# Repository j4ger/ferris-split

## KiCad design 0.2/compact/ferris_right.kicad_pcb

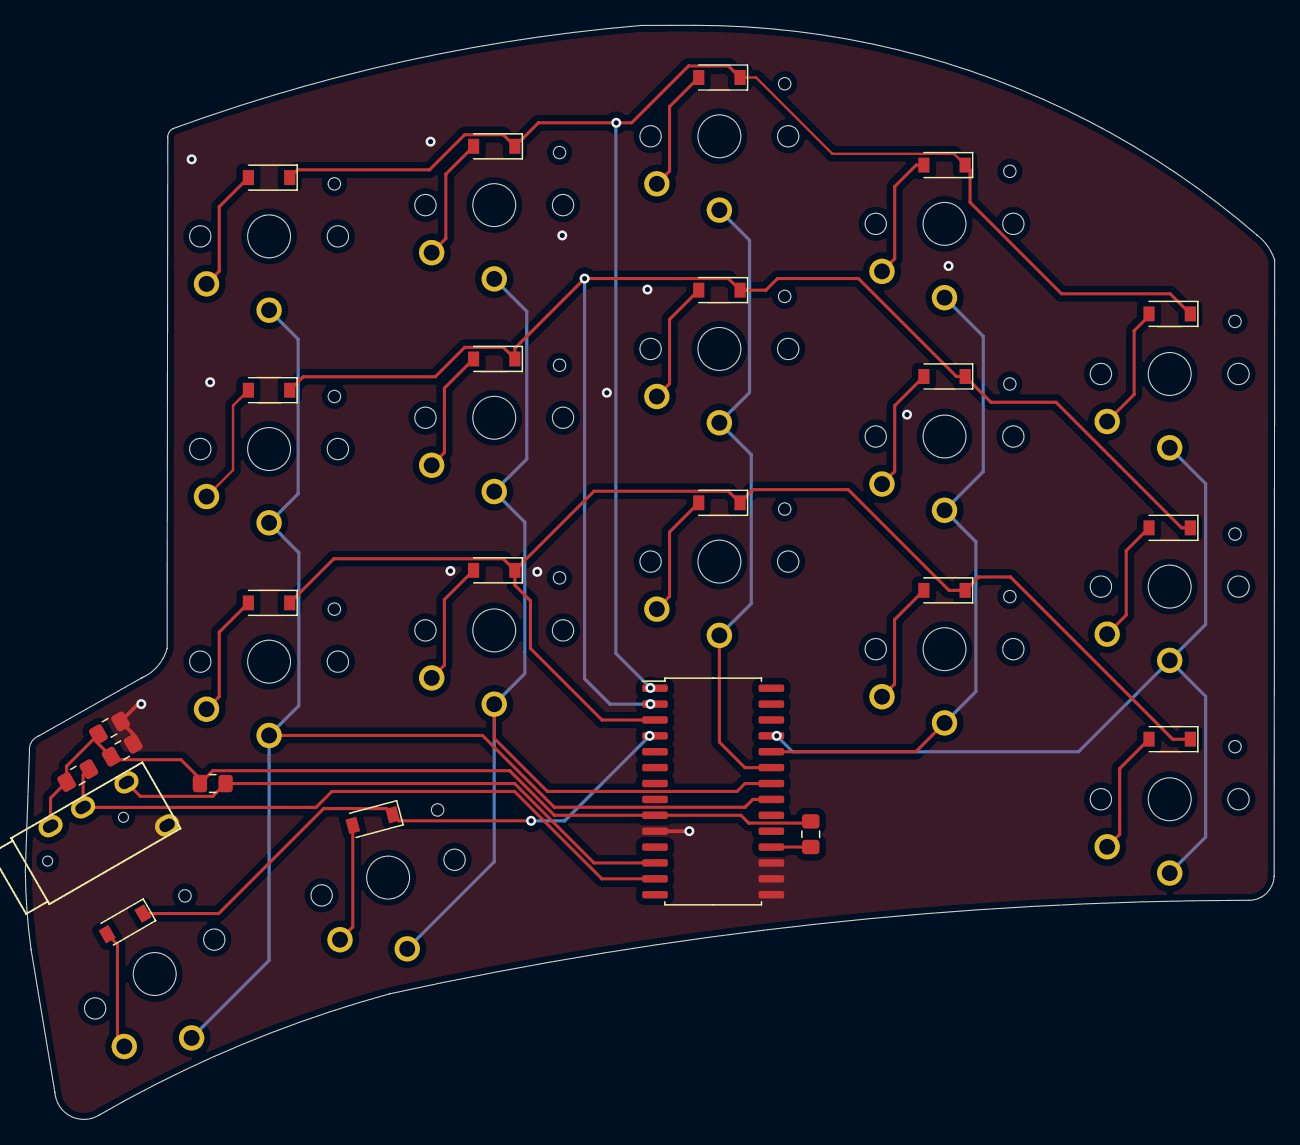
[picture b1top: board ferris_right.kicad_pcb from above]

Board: 2 copper layers, 99.9 x 87.5 mm, 41 parts (0 on the bottom side), 31 nets.

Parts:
C12, C13: 0.1uF; C_0805_2012Metric_Pad1.15x1.40mm_HandSolder
D0_5, D0_6, D0_7, D0_8, D0_9, D1_5, D1_6, D1_7, D1_8, D1_9, D2_5, D2_6, D2_7, D2_8, D2_9, D3_5, D3_6: 1N4148W; D_SOD-123
Jack1: PJ-320A; TRRS-PJ-320A
K0_5, K0_6, K0_7, K0_8, K0_9, K1_5, K1_6, K1_7, K1_8, K1_9, K2_5, K2_6, K2_7, K2_8, K2_9, K3_5, K3_6: KEYSW; Choc_PG1350_Choc_Spacing
R6: 10kΩ; R_0805_2012Metric_Pad1.15x1.40mm_HandSolder
R7, R8: 4.7kΩ; R_0805_2012Metric_Pad1.15x1.40mm_HandSolder
U2: MCP23017-E/SO; SOIC-28W_7.5x17.9mm_P1.27mm

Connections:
/col5: K0_5.1, K1_5.1, K2_5.1, K3_5.1, U2.21
/col6: K0_6.1, K1_6.1, K2_6.1, K3_6.1, U2.22
/col7: K0_7.1, K1_7.1, K2_7.1, U2.23
/col8: K0_8.1, K1_8.1, K2_8.1, U2.24
/col9: K0_9.1, K1_9.1, K2_9.1, U2.25
/row1,0: D0_5.1, D0_6.1, D0_7.1, D0_8.1, D0_9.1, U2.1
/row1,1: D1_5.1, D1_6.1, D1_7.1, D1_8.1, D1_9.1, U2.2
/row1,2: D2_5.1, D2_6.1, D2_7.1, D2_8.1, D2_9.1, U2.3
/row1,3: D3_5.1, D3_6.1, U2.4
GND: C12.1, C13.1, Jack1.S, U2.10, U2.15, U2.16, U2.17
unnamed: D0_5.2, K0_5.2
unnamed: D0_6.2, K0_6.2
unnamed: D0_7.2, K0_7.2
unnamed: D0_8.2, K0_8.2
unnamed: D0_9.2, K0_9.2
unnamed: D1_5.2, K1_5.2
unnamed: D1_6.2, K1_6.2
unnamed: D1_7.2, K1_7.2
unnamed: D1_8.2, K1_8.2
unnamed: D1_9.2, K1_9.2
unnamed: D2_5.2, K2_5.2
unnamed: D2_6.2, K2_6.2
unnamed: D2_7.2, K2_7.2
unnamed: D2_8.2, K2_8.2
unnamed: D2_9.2, K2_9.2
unnamed: D3_5.2, K3_5.2
unnamed: D3_6.2, K3_6.2
unnamed: R6.1, U2.18
VDD: C12.2, C13.2, Jack1.R2, R6.2, R7.1, R8.1, U2.9
i2c_scl_right: Jack1.T, R7.2, U2.12
i2c_sda_right: Jack1.R1, R8.2, U2.13

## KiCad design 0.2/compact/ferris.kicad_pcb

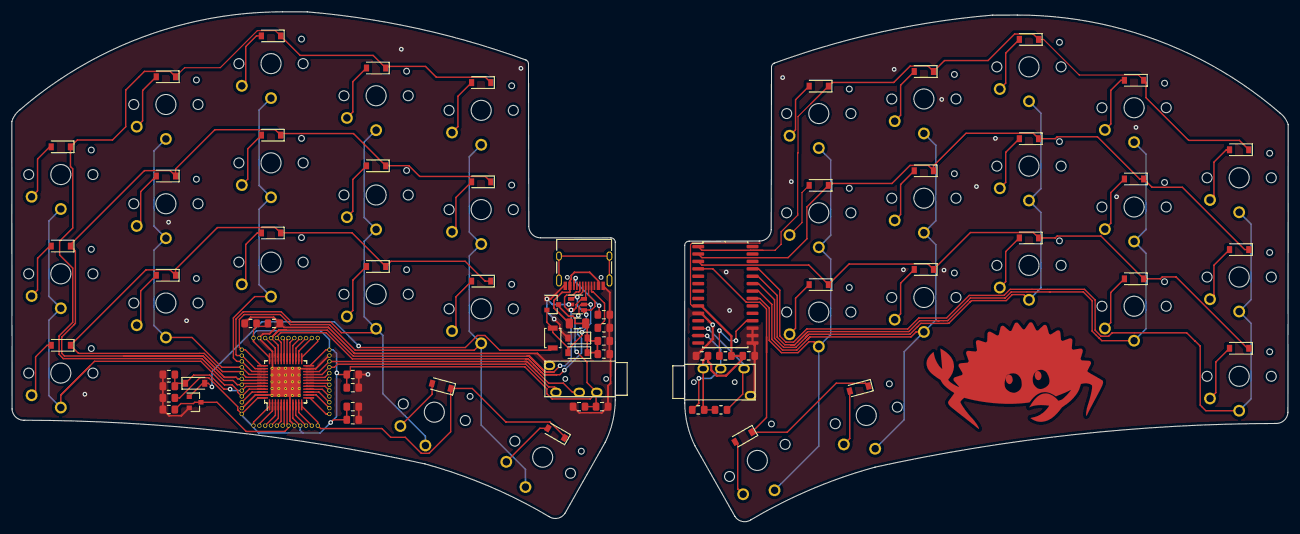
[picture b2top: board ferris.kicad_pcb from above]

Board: 2 copper layers, 218.6 x 87.3 mm, 102 parts (0 on the bottom side), 69 nets.

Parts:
C1, C2, C7: 1uF; C_0805_2012Metric_Pad1.15x1.40mm_HandSolder
C3, C8: 10uF; C_0805_2012Metric_Pad1.15x1.40mm_HandSolder
C4: 4.7nF; C_0805_2012Metric_Pad1.15x1.40mm_HandSolder
C5, C9, C10, C12, C13: 0.1uF; C_0805_2012Metric_Pad1.15x1.40mm_HandSolder
C6, C11: 4.7uF; C_0805_2012Metric_Pad1.15x1.40mm_HandSolder
D0_0, D0_1, D0_2, D0_3, D0_4, D0_5, D0_6, D0_7, D0_8, D0_9, D1_0, D1_1, D1_2, D1_3, D1_4, D1_5, D1_6, D1_7, D1_8, D1_9, D2_0, D2_1, D2_2, D2_3, D2_4, D2_5, D2_6, D2_7, D2_8, D2_9, D3, D3_3, D3_4, D3_5, D3_6: 1N4148W; D_SOD-123
D1: SMF9.0CA; D_SOD-123
D2: RB060M-30TR; D_SOD-123
F1: 500mA; Fuse_1206_3216Metric
J1: TYPE-C-31-M-12; USB_C_Receptacle_HRO_TYPE-C-31-M-12
Jack0, Jack1: PJ-320A; TRRS-PJ-320A
K0_0, K0_1, K0_2, K0_3, K0_4, K0_5, K0_6, K0_7, K0_8, K0_9, K1_0, K1_1, K1_2, K1_3, K1_4, K1_5, K1_6, K1_7, K1_8, K1_9, K2_0, K2_1, K2_2, K2_3, K2_4, K2_5, K2_6, K2_7, K2_8, K2_9, K3_3, K3_4, K3_5, K3_6: KEYSW; Choc_PG1350_Choc_Spacing
Q1: PDTC123JT,215; SOT-23
R1, R2: 5.1kΩ; R_0805_2012Metric_Pad1.15x1.40mm_HandSolder
R3, R4, R5: 100kΩ; R_0805_2012Metric_Pad1.15x1.40mm_HandSolder
R6: 10kΩ; R_0805_2012Metric_Pad1.15x1.40mm_HandSolder
R7, R8: 4.7kΩ; R_0805_2012Metric_Pad1.15x1.40mm_HandSolder
SW1: B3U-1000P; SW_SPST_B3U-1000P
U1: STM32F072CBT6; Dual_MCU_QFP_QFN_48_with_breakout_pins
U2: MCP23017-E/SO; SOIC-28W_7.5x17.9mm_P1.27mm
U3: MCP1700T-3302E/TT; SOT-23
U4: SRV05-4; SOT-23-6

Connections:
+3V3: C2.1, C5.1, C6.1, C7.1, C8.1, C9.2, C10.2, C11.2, D2.2, Jack0.R2, R4.1, SW1.1, U1.1, U1.9, U1.24, U1.36, U1.48, U3.2, U4.5
+5V: C1.1, D1.1, D2.1, F1.1, R3.1, U3.3
/D+: J1.A6, J1.B6, U1.33, U4.3, U4.6
/D-: J1.A7, J1.B7, U1.32, U4.1, U4.4
/col0: K0_0.1, K1_0.1, K2_0.1, U1.45
/col1: K0_1.1, K1_1.1, K2_1.1, U1.40
/col2: K0_2.1, K1_2.1, K2_2.1, U1.39
/col3: K0_3.1, K1_3.1, K2_3.1, K3_3.1, U1.38
/col4: K0_4.1, K1_4.1, K2_4.1, K3_4.1, U1.37
/col5: K0_5.1, K1_5.1, K2_5.1, K3_5.1, U2.21
/col6: K0_6.1, K1_6.1, K2_6.1, K3_6.1, U2.22
/col7: K0_7.1, K1_7.1, K2_7.1, U2.23
/col8: K0_8.1, K1_8.1, K2_8.1, U2.24
/col9: K0_9.1, K1_9.1, K2_9.1, U2.25
/row0,0: D0_0.1, D0_1.1, D0_2.1, D0_3.1, D0_4.1, U1.43
/row0,1: D1_0.1, D1_1.1, D1_2.1, D1_3.1, D1_4.1, U1.42
/row0,2: D2_0.1, D2_1.1, D2_2.1, D2_3.1, D2_4.1, U1.41
/row0,3: D3_3.1, D3_4.1, U1.12
/row1,0: D0_5.1, D0_6.1, D0_7.1, D0_8.1, D0_9.1, U2.1
/row1,1: D1_5.1, D1_6.1, D1_7.1, D1_8.1, D1_9.1, U2.2
/row1,2: D2_5.1, D2_6.1, D2_7.1, D2_8.1, D2_9.1, U2.3
/row1,3: D3_5.1, D3_6.1, U2.4
BOOT0: C3.1, D3.1, R5.1, U1.44
GND: C1.2, C2.2, C3.2, C4.2, C5.2, C6.2, C7.2, C8.2, C9.1, C10.1, C11.1, C12.1, C13.1, D1.2, J1.A1, J1.A12, J1.B1, J1.B12, Jack0.S, Jack1.S, Q1.2, R1.1, R2.1, R3.2, R4.2, R5.2, U1.8, U1.23, U1.35, U1.47, U1.49, U2.10, U2.15, U2.16, U2.17, U3.1, U4.2
NRST: C4.1, Q1.3, U1.7
unnamed: D0_0.2, K0_0.2
unnamed: D0_1.2, K0_1.2
unnamed: D0_2.2, K0_2.2
unnamed: D0_3.2, K0_3.2
unnamed: D0_4.2, K0_4.2
unnamed: D0_5.2, K0_5.2
unnamed: D0_6.2, K0_6.2
unnamed: D0_7.2, K0_7.2
unnamed: D0_8.2, K0_8.2
unnamed: D0_9.2, K0_9.2
unnamed: D1_0.2, K1_0.2
unnamed: D1_1.2, K1_1.2
unnamed: D1_2.2, K1_2.2
unnamed: D1_3.2, K1_3.2
unnamed: D1_4.2, K1_4.2
unnamed: D1_5.2, K1_5.2
unnamed: D1_6.2, K1_6.2
unnamed: D1_7.2, K1_7.2
unnamed: D1_8.2, K1_8.2
unnamed: D1_9.2, K1_9.2
unnamed: D2_0.2, K2_0.2
unnamed: D2_1.2, K2_1.2
unnamed: D2_2.2, K2_2.2
unnamed: D2_3.2, K2_3.2
unnamed: D2_4.2, K2_4.2
unnamed: D2_5.2, K2_5.2
unnamed: D2_6.2, K2_6.2
unnamed: D2_7.2, K2_7.2
unnamed: D2_8.2, K2_8.2
unnamed: D2_9.2, K2_9.2
unnamed: D3.2, Q1.1, SW1.2
unnamed: D3_3.2, K3_3.2
unnamed: D3_4.2, K3_4.2
unnamed: D3_5.2, K3_5.2
unnamed: D3_6.2, K3_6.2
unnamed: J1.A5, R1.2
unnamed: J1.B5, R2.2
unnamed: R6.1, U2.18
VCC: F1.2, J1.A4, J1.A9, J1.B4, J1.B9
VDD: C12.2, C13.2, Jack1.R2, R6.2, R7.1, R8.1, U2.9
i2c_scl: Jack0.T, U1.21
i2c_scl_right: Jack1.T, R7.2, U2.12
i2c_sda: Jack0.R1, U1.22
i2c_sda_right: Jack1.R1, R8.2, U2.13

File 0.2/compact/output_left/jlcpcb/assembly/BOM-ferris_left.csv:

Comment,Designator,Footprint,LCSC
KEYSW,K0_0,Choc_PG1350_Choc_Spacing,
5.1kΩ,R1,R_0805_2012Metric_Pad1.15x1.40mm_HandSolder,
1N4148W,D2_1,D_SOD-123,
KEYSW,K1_3,Choc_PG1350_Choc_Spacing,
1N4148W,D1_0,D_SOD-123,
1N4148W,D2_4,D_SOD-123,
1N4148W,D2_0,D_SOD-123,
1N4148W,D0_2,D_SOD-123,
TYPE-C-31-M-12,J1,USB_C_Receptacle_HRO_TYPE-C-31-M-12,
KEYSW,K0_1,Choc_PG1350_Choc_Spacing,
KEYSW,K2_4,Choc_PG1350_Choc_Spacing,
KEYSW,K0_3,Choc_PG1350_Choc_Spacing,
1N4148W,D1_1,D_SOD-123,
1N4148W,D0_3,D_SOD-123,
1N4148W,D3_4,D_SOD-123,
KEYSW,K2_0,Choc_PG1350_Choc_Spacing,
1N4148W,D2_2,D_SOD-123,
KEYSW,K2_3,Choc_PG1350_Choc_Spacing,
1N4148W,D3_3,D_SOD-123,
1N4148W,D1_3,D_SOD-123,
1N4148W,D1_2,D_SOD-123,
5.1kΩ,R2,R_0805_2012Metric_Pad1.15x1.40mm_HandSolder,
1N4148W,D0_0,D_SOD-123,
KEYSW,K0_4,Choc_PG1350_Choc_Spacing,
KEYSW,K1_0,Choc_PG1350_Choc_Spacing,
KEYSW,K0_2,Choc_PG1350_Choc_Spacing,
1N4148W,D1_4,D_SOD-123,
1N4148W,D0_4,D_SOD-123,
1N4148W,D0_1,D_SOD-123,
KEYSW,K3_4,Choc_PG1350_Choc_Spacing,
KEYSW,K1_1,Choc_PG1350_Choc_Spacing,
KEYSW,K1_2,Choc_PG1350_Choc_Spacing,
1N4148W,D2_3,D_SOD-123,
KEYSW,K2_1,Choc_PG1350_Choc_Spacing,
KEYSW,K1_4,Choc_PG1350_Choc_Spacing,
PJ-320A,Jack0,TRRS-PJ-320A,
KEYSW,K3_3,Choc_PG1350_Choc_Spacing,
KEYSW,K2_2,Choc_PG1350_Choc_Spacing,
500mA,F1,Fuse_1206_3216Metric,
1uF,C1,C_0805_2012Metric_Pad1.15x1.40mm_HandSolder,
1uF,C2,C_0805_2012Metric_Pad1.15x1.40mm_HandSolder,
10uF,C3,C_0805_2012Metric_Pad1.15x1.40mm_HandSolder,
4.7nF,C4,C_0805_2012Metric_Pad1.15x1.40mm_HandSolder,
0.1uF,C5,C_0805_2012Metric_Pad1.15x1.40mm_HandSolder,
4.7uF,C6,C_0805_2012Metric_Pad1.15x1.40mm_HandSolder,
1uF,C7,C_0805_2012Metric_Pad1.15x1.40mm_HandSolder,
10uF,C8,C_0805_2012Metric_Pad1.15x1.40mm_HandSolder,
0.1uF,C9,C_0805_2012Metric_Pad1.15x1.40mm_HandSolder,
0.1uF,C10,C_0805_2012Metric_Pad1.15x1.40mm_HandSolder,
4.7uF,C11,C_0805_2012Metric_Pad1.15x1.40mm_HandSolder,
SMF9.0CA,D1,D_SOD-123,
RB060M-30TR,D2,D_SOD-123,
1N4148W,D3,D_SOD-123,
"PDTC123JT,215",Q1,SOT-23,
100kΩ,R4,R_0805_2012Metric_Pad1.15x1.40mm_HandSolder,
100kΩ,R5,R_0805_2012Metric_Pad1.15x1.40mm_HandSolder,
B3U-1000P,SW1,SW_SPST_B3U-1000P,
STM32F072CBT6,U1,Dual_MCU_QFP_QFN_48_with_breakout_pins,
MCP1700T-3302E/TT,U3,SOT-23,
SRV05-4,U4,SOT-23-6,
100kΩ,R3,R_0805_2012Metric_Pad1.15x1.40mm_HandSolder,

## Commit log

2022-09-29 Attempt to shrink the size of the mini version
2022-10-29 split pcb and 3d casing
2022-11-13 3D casing
